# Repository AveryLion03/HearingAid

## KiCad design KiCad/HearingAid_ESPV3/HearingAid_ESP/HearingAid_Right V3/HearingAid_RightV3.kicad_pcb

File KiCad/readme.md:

This is the custom PCB designed for this hearing aid.

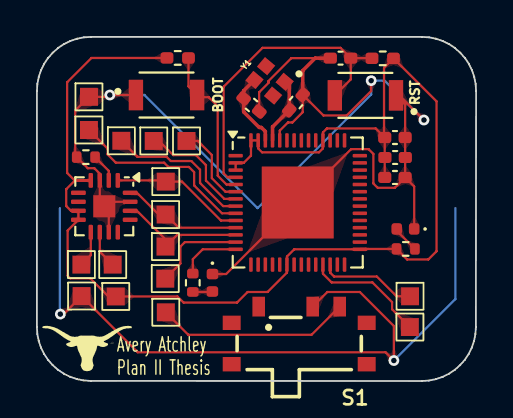
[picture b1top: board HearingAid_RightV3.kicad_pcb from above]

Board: 2 copper layers, 24.4 x 19.1 mm, 36 parts (1 on the bottom side), 24 nets.

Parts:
BT1: Battery_Cell; BatteryHolder_Keystone_3034_1x20mm_CustomCourtyard
C3: 4.7uF; C_0402_1005Metric_Pad0.74x0.62mm_HandSolder
C4: 100nF; C_0402_1005Metric_Pad0.74x0.62mm_HandSolder
C5, C8: 1uF; C_0402_1005Metric_Pad0.74x0.62mm_HandSolder
C6, C7: 10pF; C_0402_1005Metric_Pad0.74x0.62mm_HandSolder
D3: RED_LED; LED_0402_1005Metric
D4: GREEN_LED; LED_0402_1005Metric
R11, R12: 470; R_0402_1005Metric
R13: 100k; R_0402_1005Metric
R14, R15: 10k; R_0402_1005Metric_Pad0.72x0.64mm_HandSolder
RST: SW_Push; SW_B3U-1000P
S1: 450404015514
SW2: BOOT; SW_B3U-1000P
TP3, TP4, TP6, TP7, TP8, TP9, TP13, TP15, TP16, TP17, TP18, TP20, TP21, TP22, TP23, TP24: TestPoint; Mounting_Pad_Square
U5: MAX98357A; TQFN-16-1EP_3x3mm_P0.5mm_EP1.23x1.23mm
U8: ESP32-S3; QFN-56-1EP_7x7mm_P0.4mm_EP4x4mm
Y1: XRCGB40M000F1S1BR0; OSC_XRCGB40M000F1S1BR0

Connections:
B+: BT1.1 (+), S1.2, TP24.1
B-: BT1.2 (-), C3.2, C4.2, C5.2, C6.2, C7.1, C8.2, D3.1 (K), D4.1 (K), R13.2, RST.1, SW2.1, TP6.1, U5.3 (GND), U5.11 (GND), U5.15 (GND), U5.17 (PAD), U8.52 (GPIO46), U8.57 (GND)
BOOT: R15.2, SW2.2, U8.5 (GPIO0)
CLK1: TP16.1, U8.7 (GPIO2)
CLK2: TP8.1, U5.16 (BCLK), U8.11 (GPIO6)
D+: TP23.1, U8.26 (GPIO20/USB_D+)
D-: TP22.1, U8.25 (GPIO19/USB_D-)
MIC_DATA1: TP18.1, U8.9 (GPIO4)
MIC_DATA2: TP13.1, U8.13 (GPIO8)
unnamed: D3.2 (A), R11.2
unnamed: D4.2 (A), R12.1
unnamed: S1.3, TP21.1
unnamed: R13.1, U5.2 (GAIN_SLOT)
unnamed: R12.2, U8.14 (GPIO9)
unnamed: C7.2, U8.53 (XTAL_N), Y1.1
unnamed: C6.1, U8.54 (XTAL_P), Y1.3
RESET: C5.1, R14.2, RST.2, U8.4 (CHIP_PU)
SEL1: TP15.1, U8.8 (GPIO3)
SEL2: TP7.1, U5.14 (LRCLK), U8.12 (GPIO7)
SPK2_DATA: TP9.1, U5.1 (DIN), U8.10 (GPIO5)
SPK2_N: TP4.1, U5.10 (OUTN)
SPK2_P: TP3.1, U5.9 (OUTP)
SPK_DATA1: TP17.1, U8.6 (GPIO1)
VDD_ESP: C3.1, C4.1, C8.1, R11.1, R14.1, R15.1, TP20.1, U5.4 (~SD_MODE), U5.7 (VDD), U5.8 (VDD), U8.2 (VDD3P3), U8.3 (VDD3P3), U8.20 (VDD3P3_RTC), U8.29 (VDD_SPI), U8.46 (VDD3P3_CPU), U8.55 (VDDA), U8.56 (VDDA)

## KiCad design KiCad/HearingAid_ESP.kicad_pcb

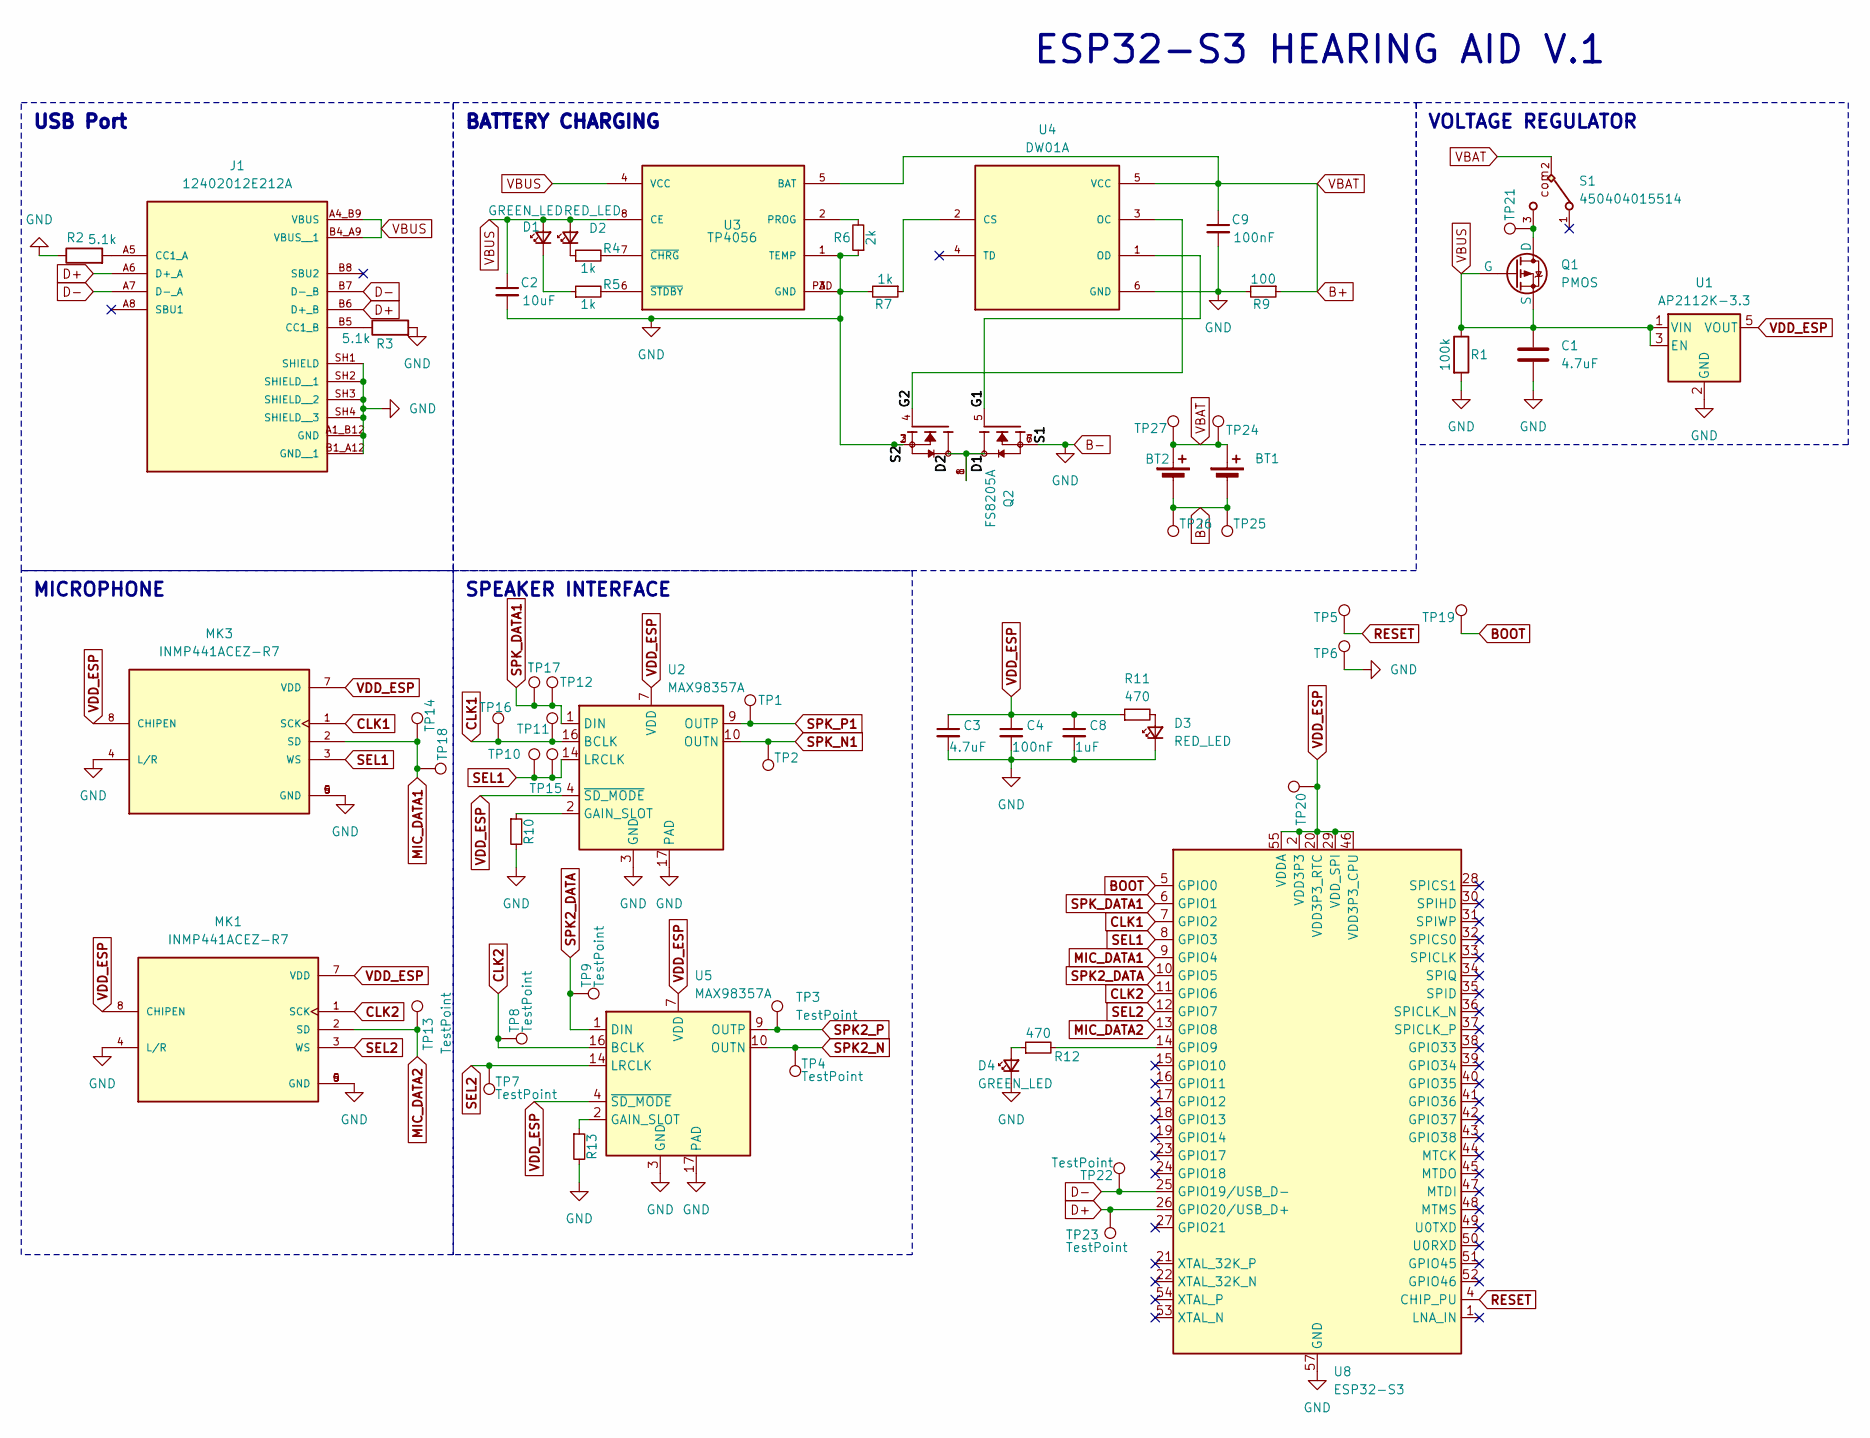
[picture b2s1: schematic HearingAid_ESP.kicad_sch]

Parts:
BT1, BT2: Battery_Cell; BatteryHolder_Keystone_3034_1x20mm
C1, C3: 4.7uF; C_0402_1005Metric_Pad0.74x0.62mm_HandSolder
C2: 10uF; C_0402_1005Metric_Pad0.74x0.62mm_HandSolder
C4, C9: 100nF; C_0402_1005Metric_Pad0.74x0.62mm_HandSolder
C8: 1uF; C_0402_1005Metric_Pad0.74x0.62mm_HandSolder
D1, D4: GREEN_LED; LED_0402_1005Metric
D2, D3: RED_LED; LED_0402_1005Metric
J1: 12402012E212A; AMPHENOL_12402012E212A; PARTREV 4
MK1, MK3: INMP441ACEZ-R7; MIC_INMP441ACEZ-R7; PARTREV 1.1
Q1: PMOS; DMP3099L-7
Q2: FS8205A; SOP65P640X120-8N; PARTREV 1.7
R1: 100k; R_0402_1005Metric_Pad0.72x0.64mm_HandSolder
R2, R3: 5.1k; R_0402_1005Metric_Pad0.72x0.64mm_HandSolder
R4, R5, R7: 1k; R_0402_1005Metric_Pad0.72x0.64mm_HandSolder
R6: 2k; R_0402_1005Metric_Pad0.72x0.64mm_HandSolder
R9: 100; R_0402_1005Metric_Pad0.72x0.64mm_HandSolder
R10, R13: 100k; R_0402_1005Metric
R11, R12: 470; R_0402_1005Metric
S1: 450404015514; PART-NUMBER 450404015514
TP1, TP2, TP3, TP4, TP5, TP6, TP7, TP8, TP9, TP10, TP11, TP12, TP13, TP14, TP15, TP16, TP17, TP18, TP19, TP20, TP21, TP22, TP23, TP24, TP25, TP26, TP27: TestPoint; Mounting_Pad_Rectangular
U1: AP2112K-3.3; SOT-23-5
U2, U5: MAX98357A; TQFN-16-1EP_3x3mm_P0.5mm_EP1.23x1.23mm
U3: TP4056; SO08-PAD-300
U4: DW01A; SOT95P280X145-6N; PARTREV 1.8
U8: ESP32-S3; QFN-56-1EP_7x7mm_P0.4mm_EP4x4mm

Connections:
/D1: Q2.1, Q2.8
/G1: Q2.5, U4.1 (OD)
/G2: Q2.4, U4.3 (OC)
B+: BT1.1 (+), BT2.1 (+), C9.1, R9.1, S1.2, TP24.1, TP27.1, U3.5 (BAT), U4.5 (VCC)
B-: BT1.2 (-), BT2.2 (-), C1.2, C2.2, C3.2, C4.2, C8.2, C9.2, D3.1 (K), D4.1 (K), J1.A1_B12 (GND), J1.B1_A12 (GND__1), J1.SH1 (SHIELD), J1.SH2 (SHIELD__1), J1.SH3 (SHIELD__2), J1.SH4 (SHIELD__3), MK1.4 (L/R), MK1.5 (GND), MK1.6 (GND), MK1.9 (GND), MK3.4 (L/R), MK3.5 (GND), MK3.6 (GND), MK3.9 (GND), Q2.2, Q2.3, Q2.6, Q2.7, R1.2, R2.1, R3.2, R6.1, R7.2, R9.2, R10.2, R13.2, TP6.1, TP25.1, TP26.1, U1.2 (GND), U2.3 (GND), U2.11 (GND), U2.15 (GND), U2.17 (PAD), U3.1 (TEMP), U3.3 (GND), U3.PAD (GND), U4.6 (GND), U5.3 (GND), U5.11 (GND), U5.15 (GND), U5.17 (PAD), U8.57 (GND)
BOOT: TP19.1, U8.5 (GPIO0)
CLK1: MK3.1 (SCK), TP11.1, TP16.1, U2.16 (BCLK), U8.7 (GPIO2)
CLK2: MK1.1 (SCK), TP8.1, U5.16 (BCLK), U8.11 (GPIO6)
D+: J1.A6 (D+_A), J1.B6 (D+_B), TP23.1, U8.26 (GPIO20/USB_D+)
D-: J1.A7 (D-_A), J1.B7 (D-_B), TP22.1, U8.25 (GPIO19/USB_D-)
MIC_DATA1: MK3.2 (SD), TP14.1, TP18.1, U8.9 (GPIO4)
MIC_DATA2: MK1.2 (SD), TP13.1, U8.13 (GPIO8)
unnamed: D1.1 (K), R5.1
unnamed: D2.1 (K), R4.1
unnamed: D3.2 (A), R11.2
unnamed: D4.2 (A), R12.1
unnamed: J1.A5 (CC1_A), R2.2
unnamed: J1.B5 (CC1_B), R3.1
unnamed: Q1.1 (D), S1.3, TP21.1
unnamed: R10.1, U2.2 (GAIN_SLOT)
unnamed: R6.2, U3.2 (PROG)
unnamed: R4.2, U3.7 (~CHRG)
unnamed: R5.2, U3.6 (~STDBY)
unnamed: R7.1, U4.2 (CS)
unnamed: R13.1, U5.2 (GAIN_SLOT)
unnamed: R12.2, U8.14 (GPIO9)
RESET: TP5.1, U8.4 (CHIP_PU)
SEL1: MK3.3 (WS), TP10.1, TP15.1, U2.14 (LRCLK), U8.8 (GPIO3)
SEL2: MK1.3 (WS), TP7.1, U5.14 (LRCLK), U8.12 (GPIO7)
SPK2_DATA: TP9.1, U5.1 (DIN), U8.10 (GPIO5)
SPK2_N: TP4.1, U5.10 (OUTN)
SPK2_P: TP3.1, U5.9 (OUTP)
SPK_DATA1: TP12.1, TP17.1, U2.1 (DIN), U8.6 (GPIO1)
SPK_N1: TP2.1, U2.10 (OUTN)
SPK_P1: TP1.1, U2.9 (OUTP)
VBUS: C1.1, C2.1, D1.2 (A), D2.2 (A), J1.A4_B9 (VBUS), J1.B4_A9 (VBUS__1), Q1.2 (G), Q1.3 (S), R1.1, U1.1 (VIN), U1.3 (EN), U3.4 (VCC), U3.8 (CE)
VDD_ESP: C3.1, C4.1, C8.1, MK1.7 (VDD), MK1.8 (CHIPEN), MK3.7 (VDD), MK3.8 (CHIPEN), R11.1, TP20.1, U1.5 (VOUT), U2.4 (~SD_MODE), U2.7 (VDD), U2.8 (VDD), U5.4 (~SD_MODE), U5.7 (VDD), U5.8 (VDD), U8.2 (VDD3P3), U8.3 (VDD3P3), U8.20 (VDD3P3_RTC), U8.29 (VDD_SPI), U8.46 (VDD3P3_CPU), U8.55 (VDDA), U8.56 (VDDA)

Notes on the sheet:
BATTERY CHARGING
MICROPHONE
SPEAKER INTERFACE
VOLTAGE REGULATOR
USB Port
ESP32-S3 HEARING AID V.1

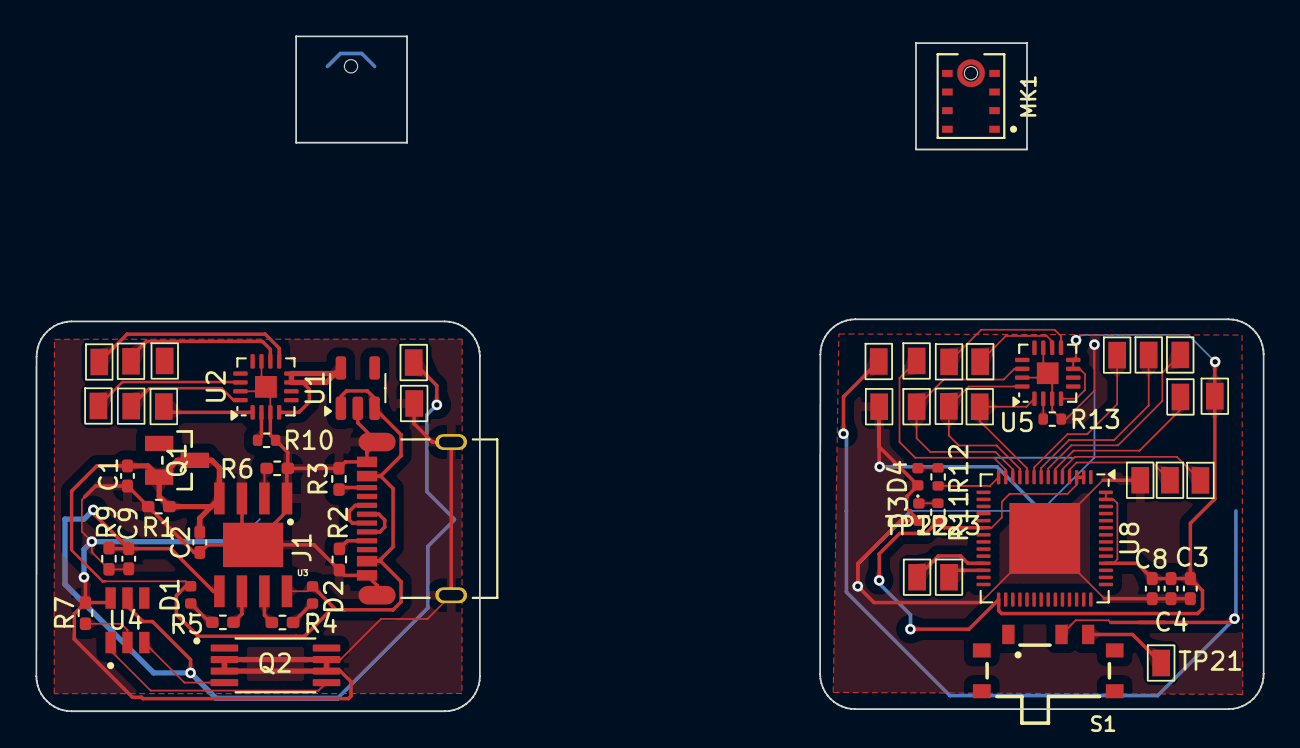
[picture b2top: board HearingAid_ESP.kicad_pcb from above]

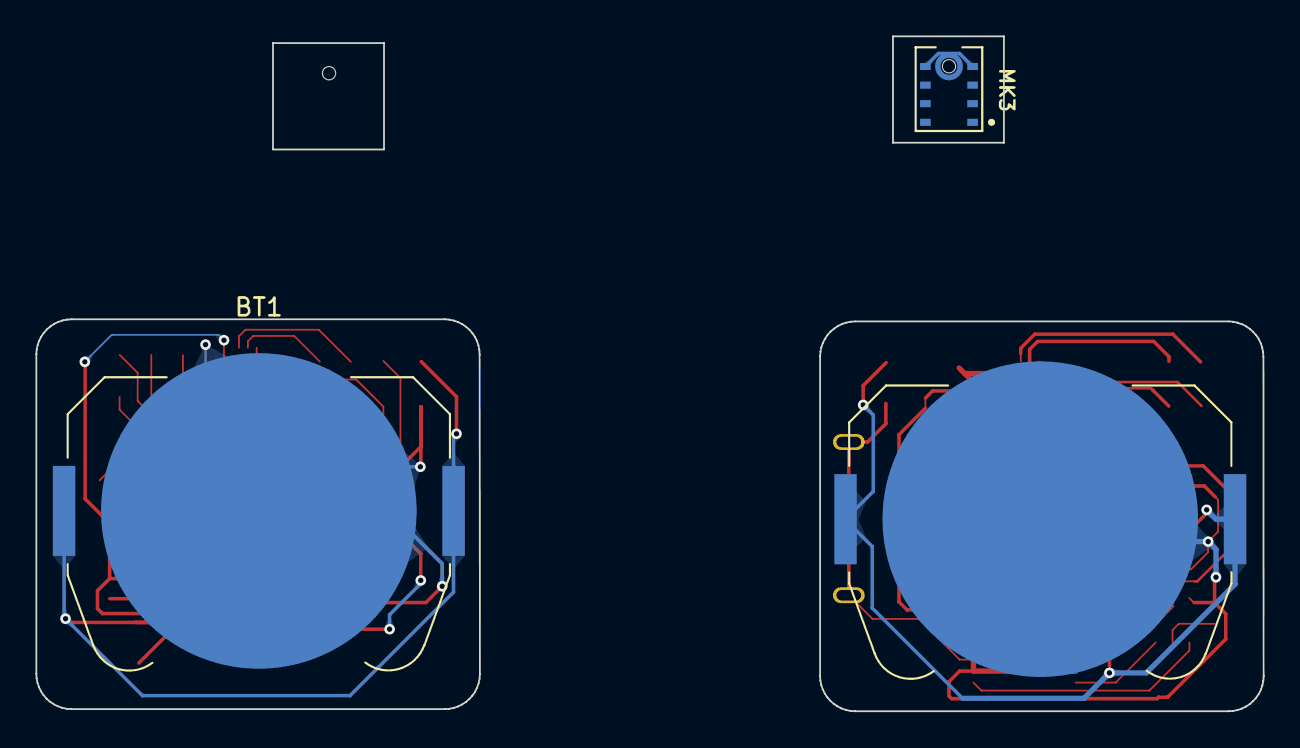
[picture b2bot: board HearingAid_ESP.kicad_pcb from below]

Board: 2 copper layers, 69.2 x 38.1 mm, 63 parts (3 on the bottom side), 37 nets.

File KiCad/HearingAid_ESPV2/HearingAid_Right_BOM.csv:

"Reference","Value","Datasheet","Footprint","Qty","DNP"
"BT1,BT2","Battery_Cell","~","Battery:BatteryHolder_Keystone_3034_1x20mm_CustomCourtyard","2",""
"C1,C3","4.7uF","~","Capacitor_SMD:C_0402_1005Metric_Pad0.74x0.62mm_HandSolder","2",""
"C2","10uF","~","Capacitor_SMD:C_0402_1005Metric_Pad0.74x0.62mm_HandSolder","1",""
"C4,C9","100nF","~","Capacitor_SMD:C_0402_1005Metric_Pad0.74x0.62mm_HandSolder","2",""
"C8","1uF","~","Capacitor_SMD:C_0402_1005Metric_Pad0.74x0.62mm_HandSolder","1",""
"D1,D4","GREEN_LED","~","LED_SMD:LED_0402_1005Metric","2",""
"D2,D3","RED_LED","~","LED_SMD:LED_0402_1005Metric","2",""
"J1","12402012E212A","","12402012E212A:AMPHENOL_12402012E212A","1",""
"MK1,MK3","INMP441ACEZ-R7","","INMP441ACEZ-R7:MIC_INMP441ACEZ-R7","2",""
"Q1","PMOS","https://ngspice.sourceforge.io/docs/ngspice-html-manual/manu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","footprints:DMP3099L-7","1",""
"Q2","FS8205A","","Package_TO_SOT_SMD:SOT-23-6","1",""
"R1,R10,R13","100k","~","-- mixed values --","3",""
"R2,R3","5.1k","~","Resistor_SMD:R_0402_1005Metric_Pad0.72x0.64mm_HandSolder","2",""
"R4,R5,R7","1k","~","Resistor_SMD:R_0402_1005Metric_Pad0.72x0.64mm_HandSolder","3",""
"R6","2k","~","Resistor_SMD:R_0402_1005Metric_Pad0.72x0.64mm_HandSolder","1",""
"R9","100","~","Resistor_SMD:R_0402_1005Metric_Pad0.72x0.64mm_HandSolder","1",""
"R11,R12","470","~","Resistor_SMD:R_0402_1005Metric","2",""
"S1","450404015514","","450404015514:450404015514","1",""
"TP1,TP2,TP3,TP4,TP5,TP6,TP7,TP8,TP9,TP10,TP11,TP12,TP13,TP14,TP15,TP16,TP17,TP18,TP19,TP20,TP21,TP22,TP23,TP24,TP25,TP27,TP28,TP29,TP30,TP31","TestPoint","~","MountingHole:Mounting_Pad_Square","30",""
"U1","AP2112K-3.3","https://www.diodes.com/assets/Datasheets/AP2112.pdf","Package_TO_SOT_SMD:SOT-23-5","1",""
"U2,U5","MAX98357A","https://www.analog.com/media/en/technical-documentation/data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","Package_DFN_QFN:TQFN-16-1EP_3x3mm_P0.5mm_EP1.23x1.23mm","2",""
"U3","TP4056","","TP4056 (1):SO08-PAD-300","1",""
"U4","DW01A","","DW01A:SOT95P280X145-6N","1",""
"U8","ESP32-S3","https://www.espressif.com/sites/default/files/documentation/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","Package_DFN_QFN:QFN-56-1EP_7x7mm_P0.4mm_EP4x4mm","1",""

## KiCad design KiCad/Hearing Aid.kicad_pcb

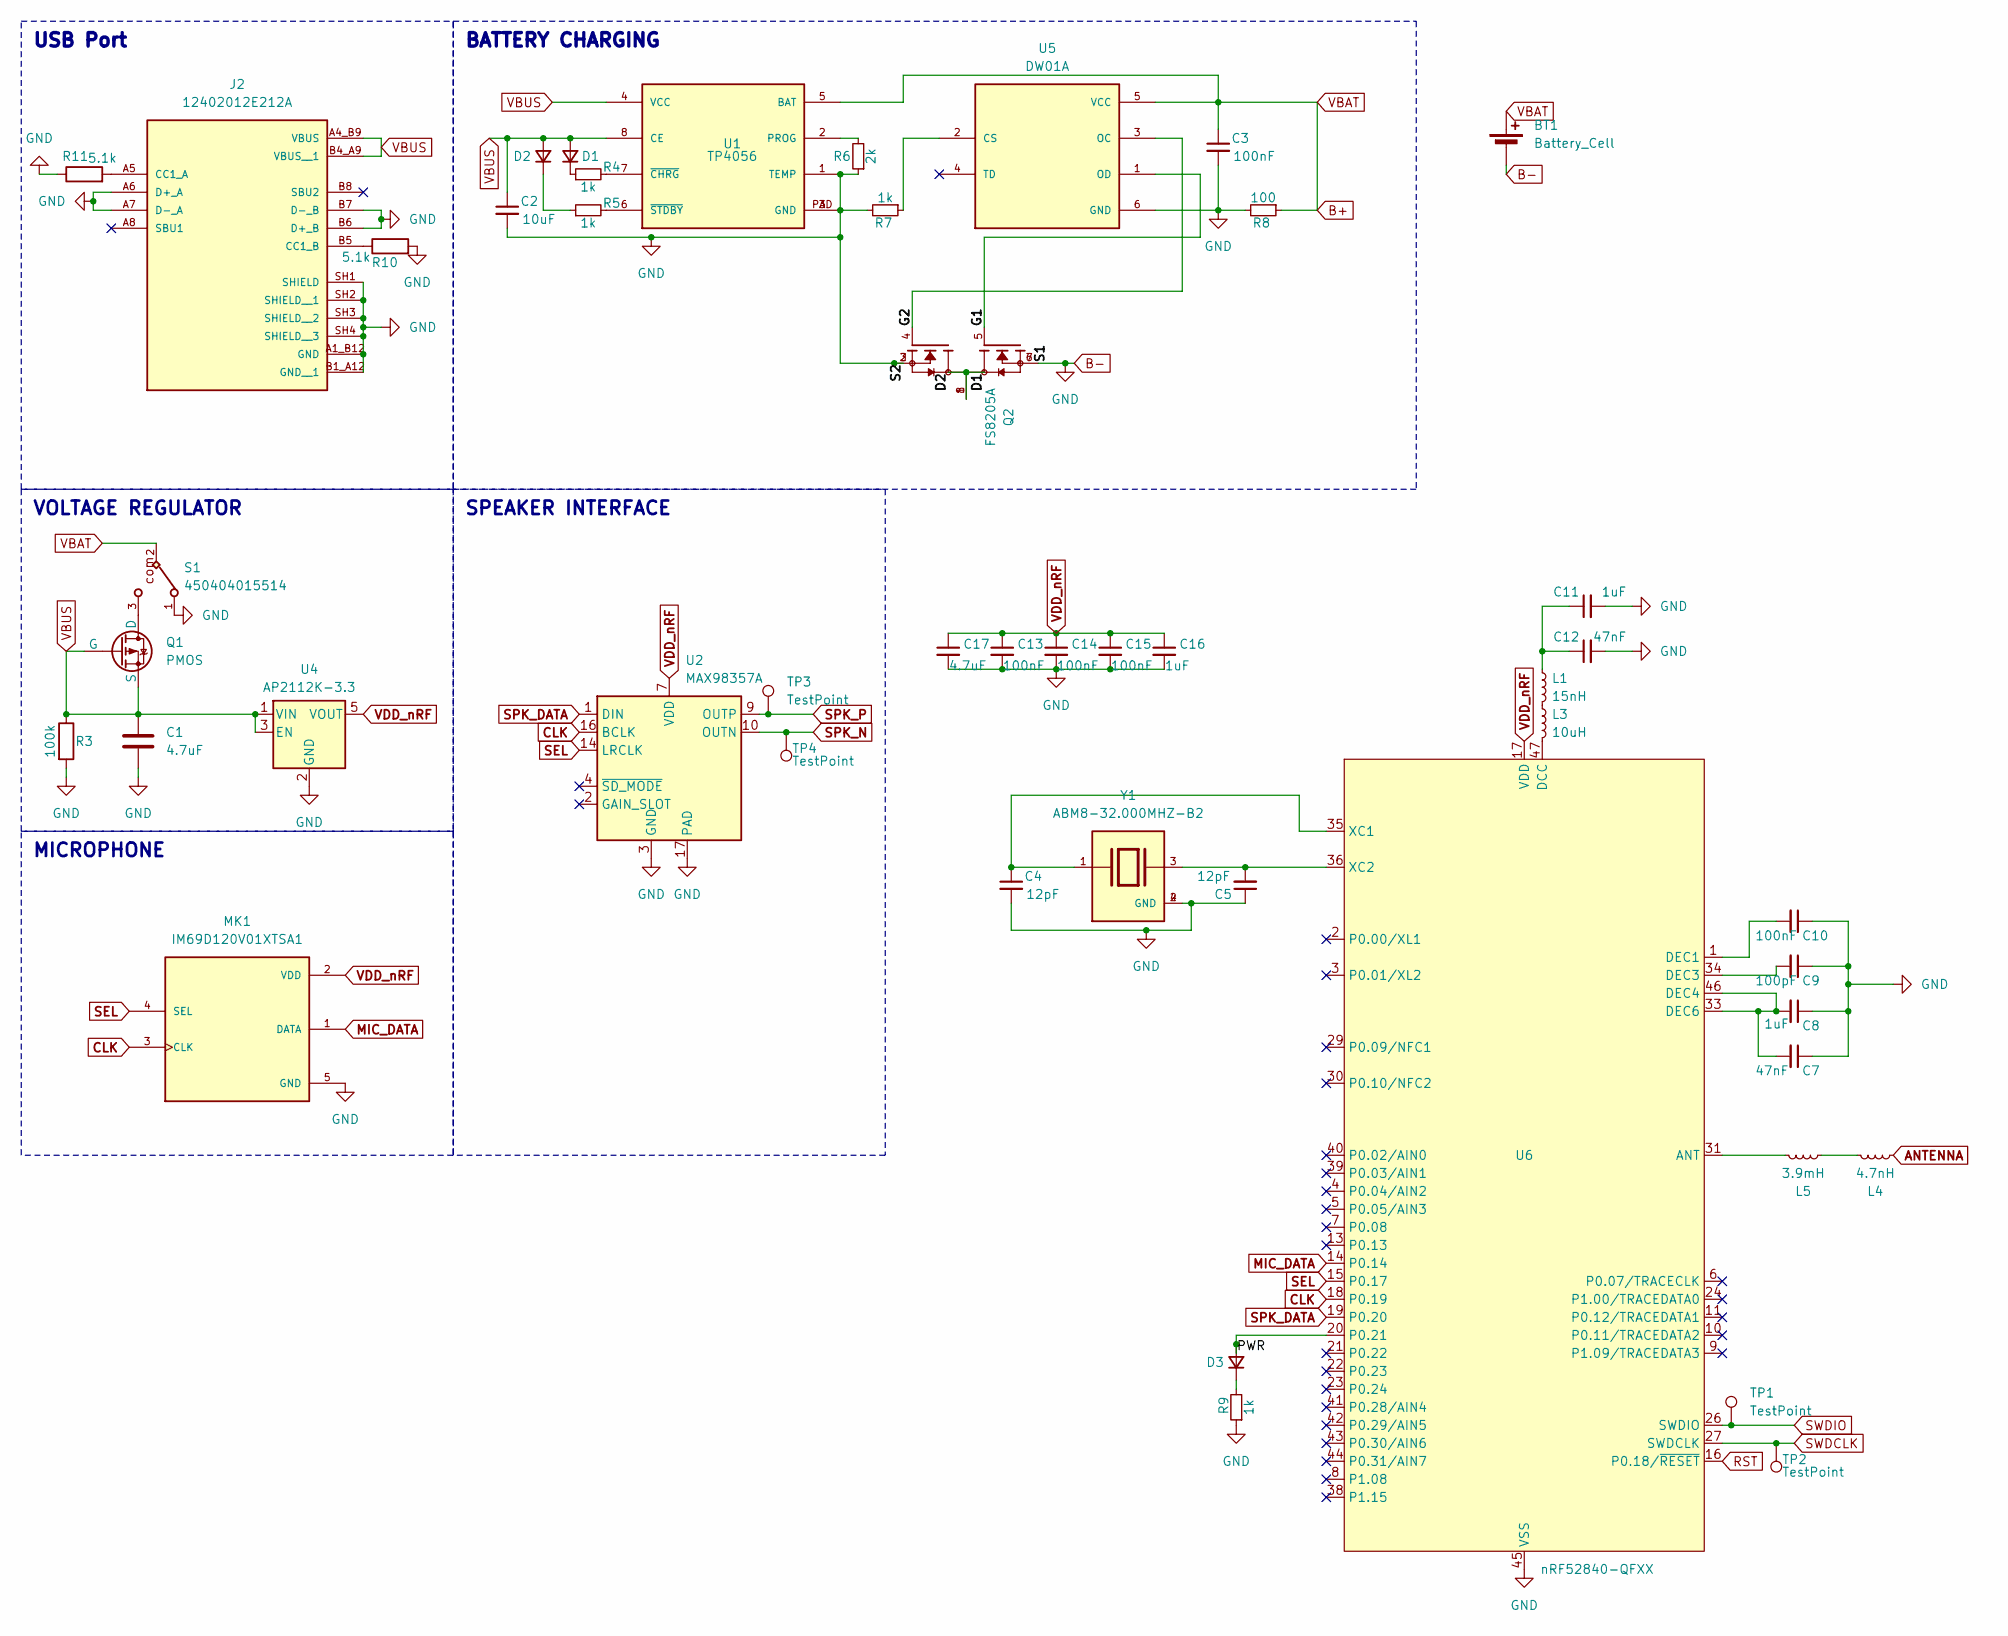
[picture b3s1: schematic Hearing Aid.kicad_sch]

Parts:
BT1: Battery_Cell; BatteryHolder_Keystone_3034_1x20mm
C1, C17: 4.7uF; C_0402_1005Metric_Pad0.74x0.62mm_HandSolder
C2: 10uF; C_0402_1005Metric_Pad0.74x0.62mm_HandSolder
C3, C10, C13, C14, C15: 100nF; C_0402_1005Metric_Pad0.74x0.62mm_HandSolder
C4, C5: 12pF; C_0402_1005Metric_Pad0.74x0.62mm_HandSolder
C7, C12: 47nF; C_0402_1005Metric_Pad0.74x0.62mm_HandSolder
C8, C11, C16: 1uF; C_0402_1005Metric_Pad0.74x0.62mm_HandSolder
C9: 100pF; C_0402_1005Metric_Pad0.74x0.62mm_HandSolder
D1, D2, D3: D_Small; D_0402_1005Metric_Pad0.77x0.64mm_HandSolder
J2: 12402012E212A; AMPHENOL_12402012E212A; PARTREV 4
L1: 15nH; L_0402_1005Metric_Pad0.77x0.64mm_HandSolder
L3: 10uH; L_0402_1005Metric_Pad0.77x0.64mm_HandSolder
L4: 4.7nH; L_0402_1005Metric_Pad0.77x0.64mm_HandSolder
L5: 3.9mH; L_0402_1005Metric_Pad0.77x0.64mm_HandSolder
MK1: IM69D120V01XTSA1; XDCR_IM69D120V01XTSA1; PARTREV 1.0
Q1: PMOS; DMP3099L-7
Q2: FS8205A; SOP65P640X120-8N; PARTREV 1.7
R3: 100k; R_0402_1005Metric_Pad0.72x0.64mm_HandSolder
R4, R5, R7, R9: 1k; R_0402_1005Metric_Pad0.72x0.64mm_HandSolder
R6: 2k; R_0402_1005Metric_Pad0.72x0.64mm_HandSolder
R8: 100; R_0402_1005Metric_Pad0.72x0.64mm_HandSolder
R10, R11: 5.1k; R_0402_1005Metric_Pad0.72x0.64mm_HandSolder
S1: 450404015514; PART-NUMBER 450404015514
TP1, TP2, TP3, TP4: TestPoint; TestPoint_Loop_D1.80mm_Drill1.0mm_Beaded
U1: TP4056; SO08-PAD-300
U2: MAX98357A; TQFN-16-1EP_3x3mm_P0.5mm_EP1.23x1.23mm
U4: AP2112K-3.3; SOT-23-5
U5: DW01A; SOT95P280X145-6N; PARTREV 1.8
U6: nRF52840-QFXX; QFN-48-1EP_6x6mm_P0.4mm_EP4.6x4.6mm
Y1: ABM8-32.000MHZ-B2; XTAL_ABM8-48.000MHZ-B2; PARTREV 44041

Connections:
/D1: Q2.1, Q2.8
/G1: Q2.5, U5.1 (OD)
/G2: Q2.4, U5.3 (OC)
/PWR: D3.2 (A), U6.20 (P0.21)
ANTENNA: L4.1
B+: BT1.1 (+), C3.1, R8.1, S1.2, U1.5 (BAT), U5.5 (VCC)
B-: BT1.2 (-), C1.2, C2.2, C3.2, C4.2, C5.1, C7.1, C8.1, C9.1, C10.1, C11.2, C12.2, C13.2, C14.2, C15.2, C16.2, C17.2, J2.A1_B12 (GND), J2.A6 (D+_A), J2.A7 (D-_A), J2.B1_A12 (GND__1), J2.B6 (D+_B), J2.B7 (D-_B), J2.SH1 (SHIELD), J2.SH2 (SHIELD__1), J2.SH3 (SHIELD__2), J2.SH4 (SHIELD__3), MK1.5 (GND), Q2.2, Q2.3, Q2.6, Q2.7, R3.2, R6.1, R7.2, R8.2, R9.1, R10.2, R11.1, S1.1, U1.1 (TEMP), U1.3 (GND), U1.PAD (GND), U2.3 (GND), U2.11 (GND), U2.15 (GND), U2.17 (PAD), U4.2 (GND), U5.6 (GND), U6.32 (VSS_PA), U6.45 (VSS), U6.49 (VSS), Y1.2 (GND), Y1.4 (GND)
CLK: MK1.3 (CLK), U2.16 (BCLK), U6.18 (P0.19)
MIC_DATA: MK1.1 (DATA), U6.14 (P0.14)
unnamed: C11.1, C12.1, L1.1
unnamed: D1.1 (K), R4.1
unnamed: D2.1 (K), R5.1
unnamed: D3.1 (K), R9.2
unnamed: J2.A5 (CC1_A), R11.2
unnamed: J2.B5 (CC1_B), R10.1
unnamed: L1.2, L3.1
unnamed: L4.2, L5.1
unnamed: Q1.1 (D), S1.3
unnamed: R6.2, U1.2 (PROG)
unnamed: R4.2, U1.7 (~CHRG)
unnamed: R5.2, U1.6 (~STDBY)
unnamed: R7.1, U5.2 (CS)
unnamed: L5.2, U6.31 (ANT)
unnamed: L3.2, U6.47 (DCC)
unnamed: C10.2, U6.1 (DEC1)
unnamed: C9.2, U6.34 (DEC3)
unnamed: C7.2, C8.2, U6.33 (DEC6), U6.46 (DEC4)
unnamed: C4.1, U6.35 (XC1), Y1.1
unnamed: C5.2, U6.36 (XC2), Y1.3
RST: U6.16 (P0.18/~RESET)
SEL: MK1.4 (SEL), U2.14 (LRCLK), U6.15 (P0.17)
SPK_DATA: U2.1 (DIN), U6.19 (P0.20)
SPK_N: TP4.1, U2.10 (OUTN)
SPK_P: TP3.1, U2.9 (OUTP)
SWDCLK: TP2.1, U6.27 (SWDCLK)
SWDIO: TP1.1, U6.26 (SWDIO)
VBUS: C1.1, C2.1, D1.2 (A), D2.2 (A), J2.A4_B9 (VBUS), J2.B4_A9 (VBUS__1), Q1.2 (G), Q1.3 (S), R3.1, U1.4 (VCC), U1.8 (CE), U4.1 (VIN), U4.3 (EN)
VDD_nRF: C13.1, C14.1, C15.1, C16.1, C17.1, MK1.2 (VDD), U2.7 (VDD), U2.8 (VDD), U4.5 (VOUT), U6.12 (VDD), U6.17 (VDD), U6.25 (VDD), U6.37 (VDD), U6.48 (VDD)

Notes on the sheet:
SPEAKER INTERFACE
MICROPHONE
VOLTAGE REGULATOR
BATTERY CHARGING
USB Port

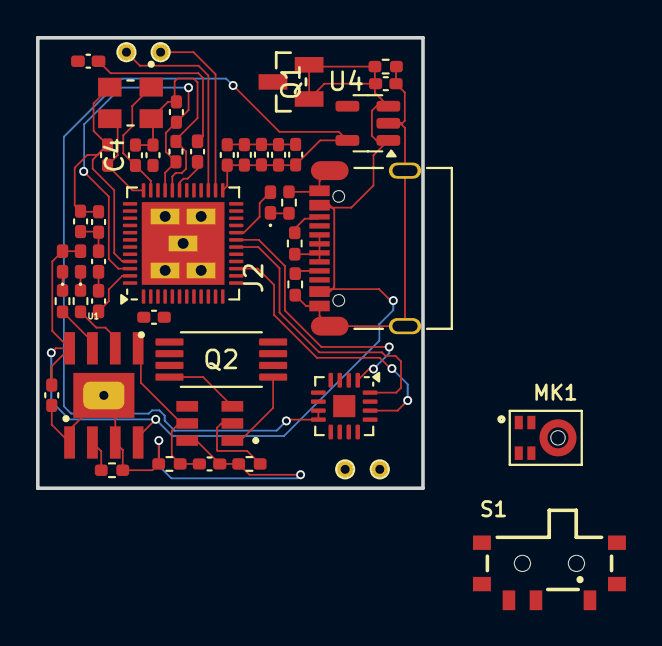
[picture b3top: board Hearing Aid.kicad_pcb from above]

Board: 2 copper layers, 21.4 x 25.0 mm, 48 parts (1 on the bottom side), 36 nets.

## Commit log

2025-01-22 Create hearingaid_testy.ino
    Test code for nRF52840 for a hearing aid design. Using I2S for input (microphone) and output (speaker). Debugging using blinking LED.
2025-02-05 Create wearable_prototype
2025-02-05 Rename wearable_prototype to wearable_prototype.ino
2025-02-08 pwm/timer support
2025-02-19 Updated Hearing Aid
2025-02-19 Updating files
2025-02-19 Removed microphone footprint
2025-03-07 Updated hearing aid files

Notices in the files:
parts and their libraries:
Copyright 2016 Accelerated Designs. All rights reserved.
